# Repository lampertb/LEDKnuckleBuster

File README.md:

[gif]: https://github.com/lampertb/LEDKnuckleBuster/blob/master/Images/touchExample.gif "LED Knuckle Buster In Action"
[datasheet]: https://github.com/lampertb/LEDKnuckleBuster/blob/master/Images/datasheet.png "Darlington NPN Datasheet"
[dxfExample]: https://github.com/lampertb/LEDKnuckleBuster/blob/master/Images/dxfExample.png "Exporting DXF Design"
[equation1]: https://github.com/lampertb/LEDKnuckleBuster/blob/master/Images/equation1.png "Base current equation"
[equation2]: https://github.com/lampertb/LEDKnuckleBuster/blob/master/Images/equation2.png "Base current equation"
[equation3]: https://github.com/lampertb/LEDKnuckleBuster/blob/master/Images/equation3.png "Base current equation"

[handFist]: https://github.com/lampertb/LEDKnuckleBuster/blob/master/Images/handFist.jpg "LED Knuckle Buster In Action"
[layout]: https://github.com/lampertb/LEDKnuckleBuster/blob/master/Images/layout.png "Board layout with fill"
[productPhoto]: https://github.com/lampertb/LEDKnuckleBuster/blob/master/Images/productPhoto.jpg "LED Knuckle Buster In Action"
[schematic]: https://github.com/lampertb/LEDKnuckleBuster/blob/master/Images/schematic.png "LED Knuckle Buster Schematic"

![alt text][gif]

# LED Knuckle Busters, light up your fists!
## By Ben Lampert

Designed and manufactured by Ben Lampert at Chicago's mHub maker space (https://mhubchicago.com/) these LED's brass knuckles are a fun toy to play with. Conductive finger holes turn on high gain transistors that lights up LED's based on the strength of the grip; just put your fingers through the hole and squeeze!

* Features:
  * Brass knuckle finger spacing fits most adults and children.
  * 100% Analog circuitry features low power operation when not in use.
  * Touch sensitive design, just make a fist to turn on the LED's!

* Requires:
  * Blue LED Brass Knuckle board (.brd files available)
  * Parts http://www.digikey.com/short/q8q7pt

* Specs
  * Height: Approx 115mm
  * Width: Approx 50mm
  * Powered by two coin cell batteries

## Project Details:

The LED Knuckle Buster mechanical and board outline was originally inspired by this thingiverse brass knuckle.
https://www.thingiverse.com/thing:1160010

I decided to make an LED version, and after downloading used solidworks to create and exporting a DXF of the outer perimeter of the model. This DXF was then important as layer 20 (board outline) in eagle to create the PCB board outline.

![alt text][dxfExample]

The circuit I think it pretty clever. I originally thought to use a microcontroller and a technique similar to the mAkey mAkey (https://makeymakey.com/). However, it seems like I put MCU’s on everything these days, so I revisited a 100% analog design.

What I came up with I think it simple and clever. The copper on the backside of the board is a VCC plan, as the fingers extend through the holes that make contact with the base of a darlignton pair. Given you skin resistivity is ~100k (https://www.ncbi.nlm.nih.gov/pmc/articles/PMC2763825/) you get a small amount of current running through your fingers.

Just as a ballpark, that current using a Darlington Pair is approximately:

![alt text][equation1]

![alt text][equation2]

![alt text][equation3]

Reviewing the cheapest Darlington Pair NPN available on Digikey
https://www.diodes.com/assets/Datasheets/ds30047.pdf

![alt text][datasheet]

This has a gain of 5,000-10,000. So our 46uA base current becomes 23-46mA of current. Not bad for small leakage through your finger!

That current is plenty to turn on a LED, so with that in mind this is the final circuit I designed.

![alt text][schematic]
![alt text][layout]

Rev A:
Forgot to connect the via for VCC to connect to the other side of the board, whoop!
Also, forgot a pull down on the base which caused FING4 LED to always be on.

Rev B:
Everything is tested ok! Time to Ship It!

![alt text][productPhoto]

![alt text][handFist]

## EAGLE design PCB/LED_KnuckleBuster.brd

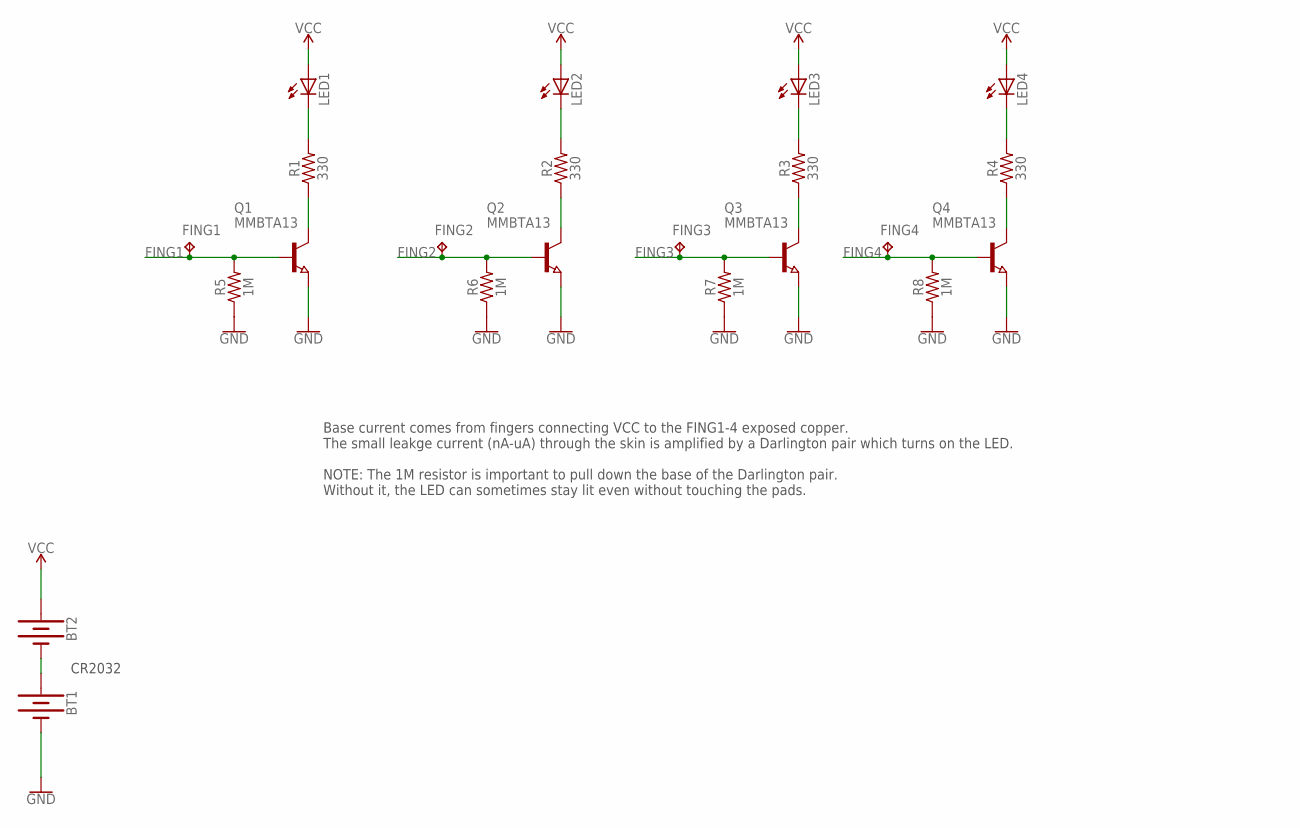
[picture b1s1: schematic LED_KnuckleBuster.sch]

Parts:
BT1, BT2: BATTERY-20MM_SMD_4LEGS; BATTCON_20MM_4LEGS
FING1, FING2, FING3, FING4: TPB2,54; B2,54
LED1, LED2, LED3, LED4: LEDCHIPLED_0805; CHIPLED_0805
Q1, Q2, Q3, Q4: MMBTA13; SOT23
R1, R2, R3, R4: 330; 0603
R5, R6, R7, R8: 1M; 0603

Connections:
FING1: FING1.TP, Q1.1 (B), R5.2
FING2: FING2.TP, Q2.1 (B), R6.2
FING3: FING3.TP, Q3.1 (B), R7.2
FING4: FING4.TP, Q4.1 (B), R8.2
GND: BT1.NEGATIVE (-), Q1.2 (E), Q2.2 (E), Q3.2 (E), Q4.2 (E), R5.1, R6.1, R7.1, R8.1
unnamed: Q1.3 (C), R1.1
unnamed: LED1.C, R1.2
unnamed: Q2.3 (C), R2.1
unnamed: LED2.C, R2.2
unnamed: Q3.3 (C), R3.1
unnamed: LED3.C, R3.2
unnamed: Q4.3 (C), R4.1
unnamed: LED4.C, R4.2
unnamed: BT1.POSITIVE@1 (+), BT1.POSITIVE@2 (+), BT1.POSITIVE@3 (+), BT1.POSITIVE@4 (+), BT2.NEGATIVE (-)
VCC: BT2.POSITIVE@1 (+), BT2.POSITIVE@2 (+), BT2.POSITIVE@3 (+), BT2.POSITIVE@4 (+), LED1.A, LED2.A, LED3.A, LED4.A

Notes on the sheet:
Base current comes from fingers connecting VCC to the FING1-4 exposed copper. The small leakge current (nA-uA) through the skin is amplified by a Darlington pair which turns on the LED. NOTE: The 1M resistor is important to pull down the base of the Darlington pair. Without it, the LED can sometime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
CR2032

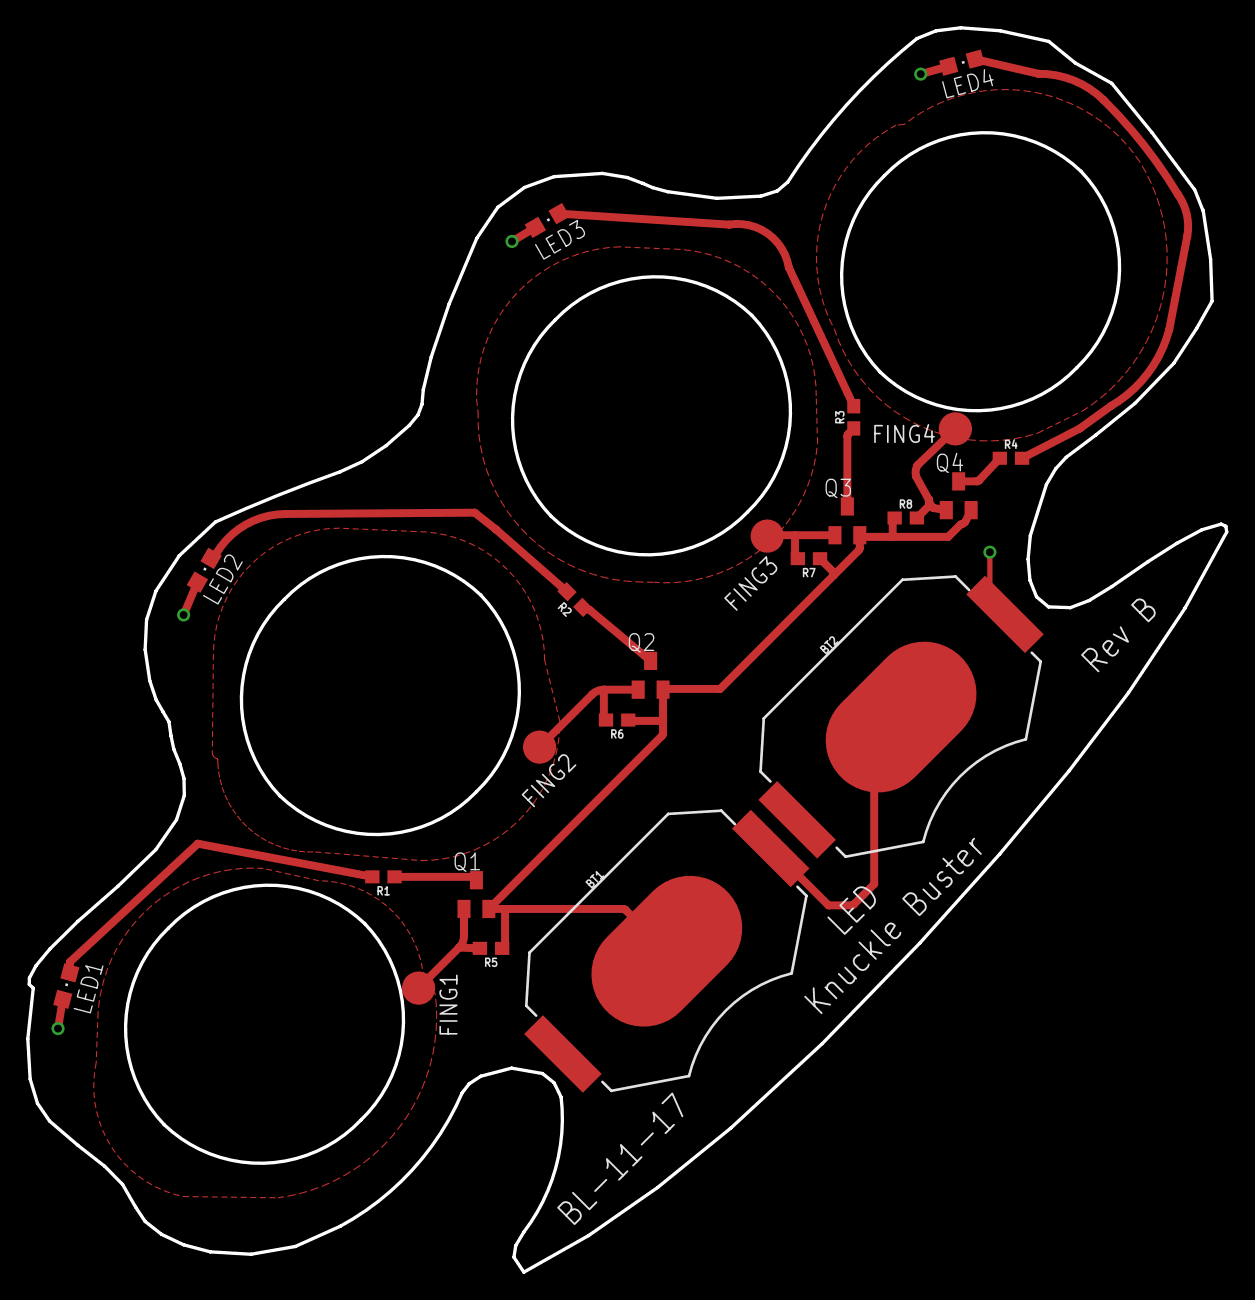
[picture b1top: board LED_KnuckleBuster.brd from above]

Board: 2 copper layers, 91.7 x 95.2 mm, 22 parts (0 on the bottom side), 15 nets.

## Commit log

2018-01-06 Added images and design files
2018-01-06 Fixed image reference
2018-01-06 updated markdown on readme
2018-01-06 Fixed issue with image reference in markdown
2018-01-06 Misc changes to markdown
2018-01-06 Polishing list on markdown of readme
2018-01-06 Reorg readme
2018-01-06 Added license file

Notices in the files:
parts and their libraries:
SparkFun-Batteries: Licensing: Creative Commons ShareAlike 4.0 International - https://creativecommons.org/licenses/by-sa/4.0
